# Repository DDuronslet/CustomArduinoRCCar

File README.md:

# CustomArduinoRCCar
Custom RC Car built with an arduino, controlled by a PS4 controller.

Transmitter built using an arduino uno, nrf24l01+ with a 3.3 voltage regulator, 9V battery with switch, and 5K potentiometer.
Reciever built with a 16hz arduino pro micro(uploaded as an arduino leonardo eth),  nrf24l01+ with a 3.3 voltage regulator, 9V battery powering the arduino, and a on board Li-ion battery to power the motor driver, dc motor, servo(buck boost set to 5V).

Motor Driver: TB9051FTG Single Brushed DC Motor Driver Carrier https://www.pololu.com/product/2997
The servo and dc motor were already on board the original RC car which the original reciever was removed.

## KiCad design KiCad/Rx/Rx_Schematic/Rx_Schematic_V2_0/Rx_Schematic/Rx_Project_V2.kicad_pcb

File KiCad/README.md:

# CustomArduinoRCCar_PCBs
This will be the folder to contain all of my KiCAD pcb designs.

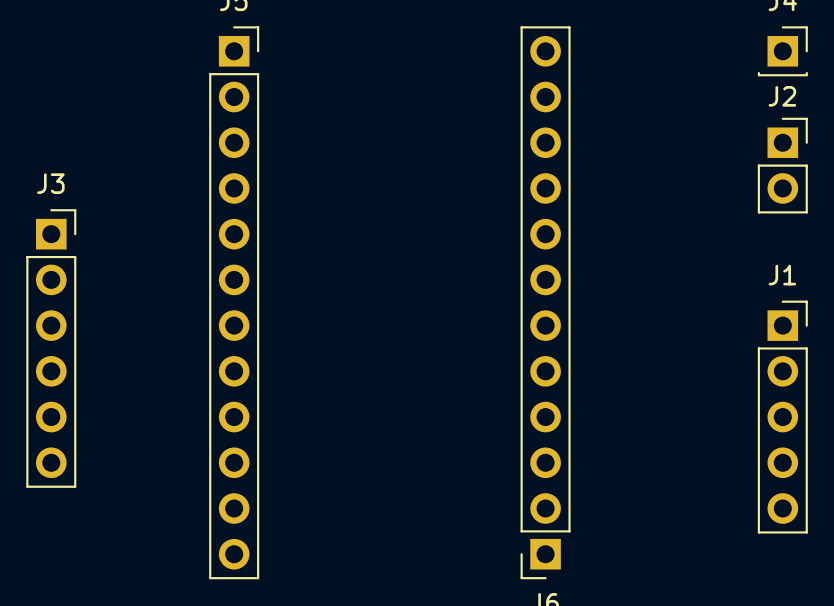
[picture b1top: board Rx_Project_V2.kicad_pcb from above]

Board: 2 copper layers, 10 parts (0 on the bottom side), 12 nets, no tracks yet.

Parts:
H1, H2, H3, H4: MountingHole; MountingHole_3.2mm_M3
J1: Conn_01x05; PinSocket_1x05_P2.54mm_Vertical
J2: Conn_01x02; PinSocket_1x02_P2.54mm_Vertical
J3: Conn_01x06; PinSocket_1x06_P2.54mm_Vertical
J4: Conn_01x02; PinSocket_1x01_P2.54mm_Vertical
J5, J6: Conn_01x12; PinSocket_1x12_P2.54mm_Vertical

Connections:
GND: J2.2, J3.1, J5.3, J5.4
unnamed: J1.1, J6.3
unnamed: J1.2, J6.2
unnamed: J1.3, J6.4
unnamed: J1.4, J6.5
unnamed: J1.5, J6.6
unnamed: J2.1, J6.7
unnamed: J3.2, J6.8
unnamed: J3.3, J6.1
unnamed: J3.4, J5.8
unnamed: J3.5, J5.9
unnamed: J3.6, J4.1

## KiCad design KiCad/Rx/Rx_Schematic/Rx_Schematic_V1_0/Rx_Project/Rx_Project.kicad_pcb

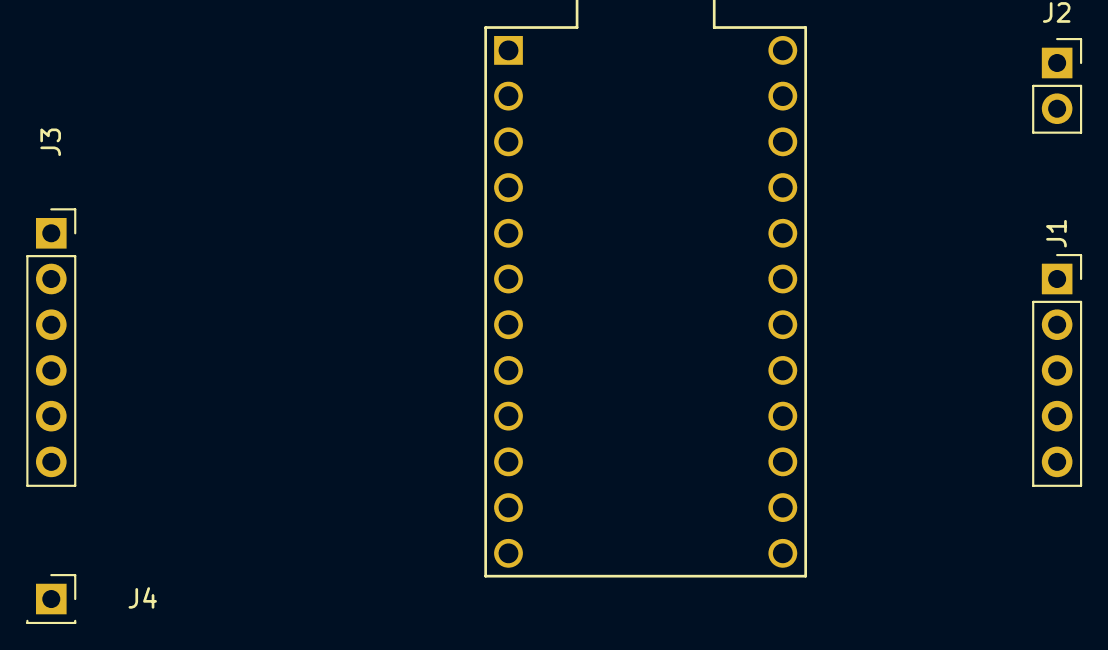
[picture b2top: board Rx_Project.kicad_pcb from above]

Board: 2 copper layers, 9 parts (0 on the bottom side), 11 nets, no tracks yet.

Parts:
H1, H2, H3, H4: MountingHole; MountingHole_3.2mm_M3
J1: Conn_01x05; PinSocket_1x05_P2.54mm_Vertical
J2: Conn_01x02; PinSocket_1x02_P2.54mm_Vertical
J3: Conn_01x06; PinSocket_1x06_P2.54mm_Vertical
J4: Conn_01x02; PinSocket_1x01_P2.54mm_Vertical
U1: ProMicro

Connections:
GND: J2.2, J3.1, U1.3 (GND), U1.4 (GND)
unnamed: J1.1, J1.2, U1.14 (B2), U1.15 (B3)
unnamed: J1.3, U1.16 (B1)
unnamed: J1.4, U1.17 (F7)
unnamed: J1.5, U1.18 (F6)
unnamed: J2.1, U1.19 (F5)
unnamed: J3.2, U1.20 (F4)
unnamed: J3.3, U1.13 (B6)
unnamed: J3.4, U1.8 (C6)
unnamed: J3.5, U1.9 (D7)
unnamed: J3.6, J4.1

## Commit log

2023-03-02 Updated folders
2023-03-02 Added SpeedAdjust
    Added array values 9-12 to be used with speed adjustment, added code for SpeedAdjust on rx and updated array values to 13 instead of 9
2023-03-02 Added Serial Print for SpeedAdjust
2023-03-02 Revert "Added Serial Print for SpeedAdjust"
    This reverts commit 4e2cd502759358e1a0d656ba48e68f5262eff252.
2023-03-02 Revert "Added SpeedAdjust"
    This reverts commit 5e436f546585fd83684232c679e175a56cd96971.
2023-03-03 Added constrainedSpeedAdjust
2023-03-03 Tidied code, updated array values
2023-03-03 Updated SpeedAdjust to int instead of float
2023-03-03 Finished SpeedAdjust on Tx Side
2023-03-03 Prevented values of 5 and 0 for speed limiter
2023-03-03 Added SpeedLimiter to rx, cleaned up code
2023-03-03 SpeedAdjust added and updated
2023-03-30 Matched Rx to Tx code
    Updated Rx code to work with current tx code, verified working aside from speed limiter not working as intended
2023-03-31 Removing Motor Carrier Library, adding 2nd code
    Rx codde 2.0 to remove motor library and manually address pwm and en pins
2023-03-31 Updated pin layout on rx
    Pin 9 on arduino pro micro not working as pwm as intended, swap pwm to pins 5 and 6 fixed issue
2023-04-04 Added count for disconnection
    Added count on both tx and rx to make sure if connection is lost the rx will stop the motor.
2023-04-04 Complied Rx
    Fixed code to pass compiling
2023-04-04 Updated rx to set servo to default on boot
2023-07-05 Added ReadMe for KiCad designs
2023-07-06 Updated Folder
2023-07-06 Updated folder layout
2023-07-06 Added data sheets and symbol for motor driver
2023-07-06 Updated schematic
2023-07-06 Updated Rx schematic
2023-07-11 Started new drawing
2023-07-11 Updated drawing
2023-07-11 Updated Rx drawing
2023-07-14 ReCreated Rx Project, and reimported libraries
2023-07-27 Schematic finished
2023-08-08 Remade file to remove nano and add connector pins in place
2023-08-17 updated page settings
